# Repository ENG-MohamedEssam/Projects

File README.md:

# Projects
This repository contains most of the projects i made during the last 4 years,
whether those projects were software (AVR32, ARM, Arduino) or Hardware . 

Note that nearly all the files presented whether it was Software or Hardware was created by me.

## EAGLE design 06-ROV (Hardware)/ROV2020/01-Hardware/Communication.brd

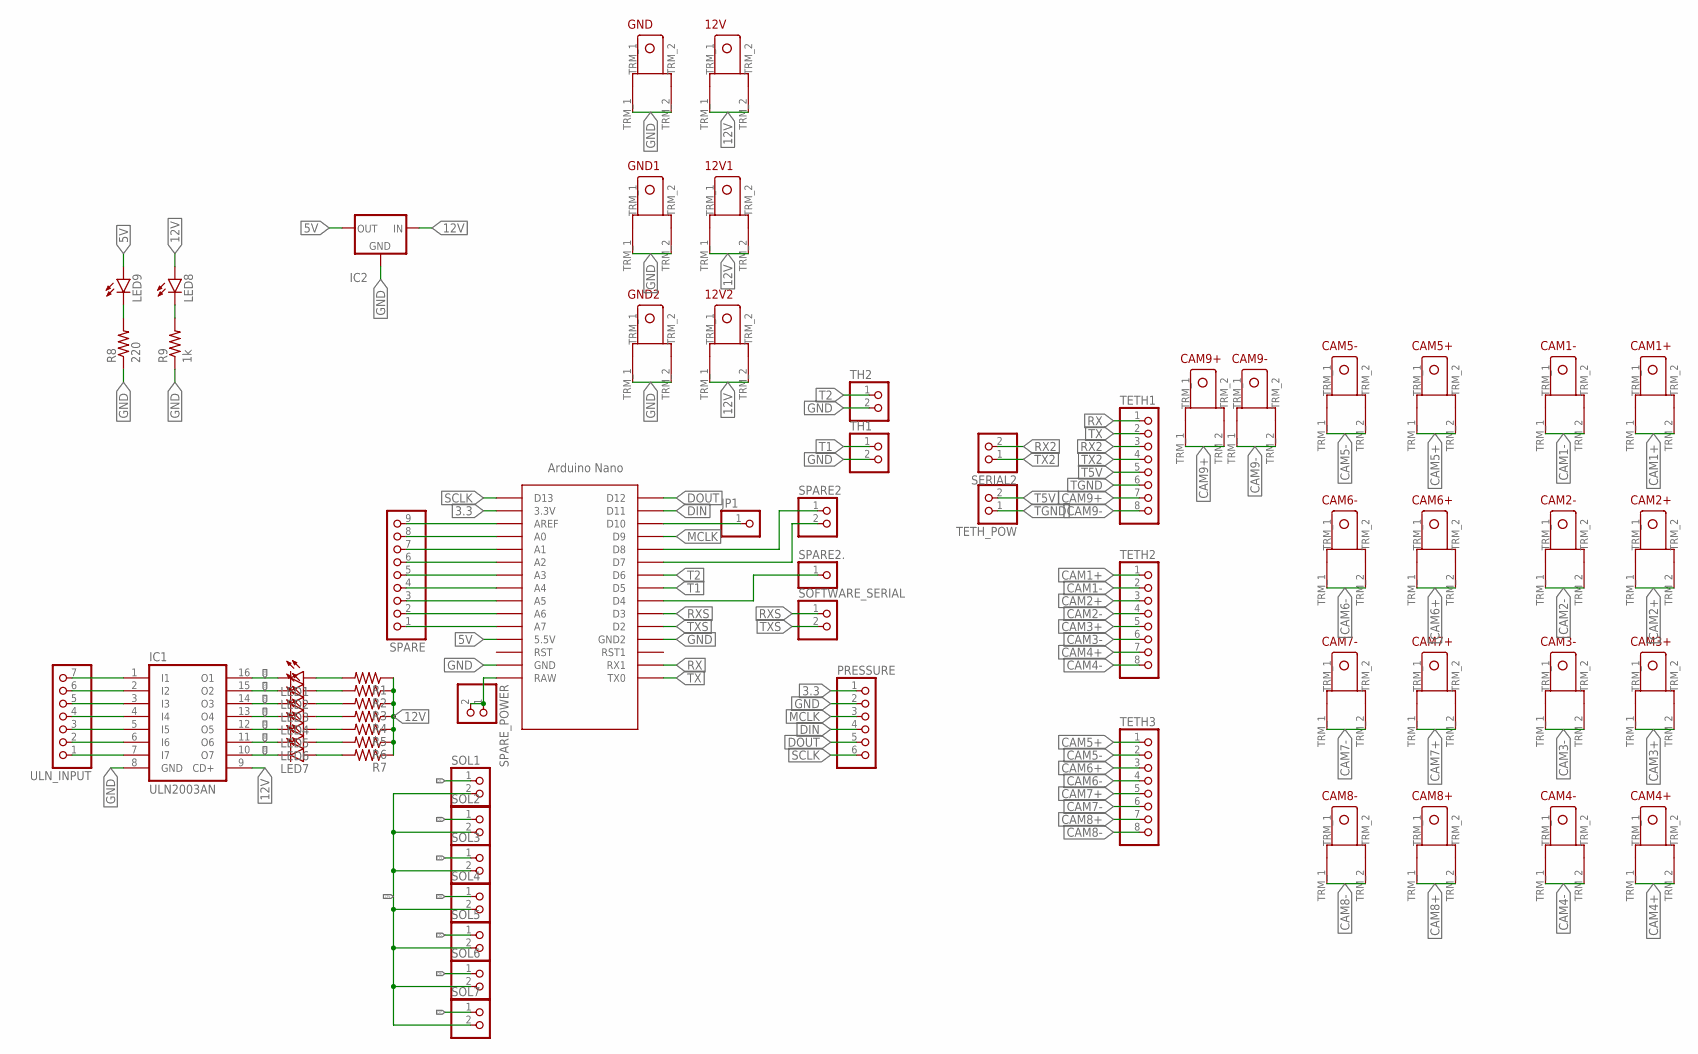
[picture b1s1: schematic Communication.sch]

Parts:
12V, 12V1, 12V2: TERMINAL_EDITED
CAM1+, CAM1-, CAM2+, CAM2-, CAM3+, CAM3-, CAM4+, CAM4-, CAM5+, CAM5-, CAM6+, CAM6-, CAM7+, CAM7-, CAM8+, CAM8-, CAM9+, CAM9-: TERMINAL_EDITED
GND, GND1, GND2: TERMINAL_EDITED
IC1: ULN2003AN; DIL16
IC2: 78XX-METAL; TO3-79
JP1: PINHD-1X1; 1X01
LED1, LED2, LED3, LED4, LED5, LED6, LED7, LED8, LED9: LED5MM
PRESSURE: PINHD-6_DATA; 1X06_DATA
R1, R2, R3, R4, R5, R6, R7: R-US_0204/7; 0204/7
R8: 220; 0204/7
R9: 1k; 0204/7
SERIAL2: PINHD-2_DATA; 1X02_DATA
SOFTWARE_SERIAL: PINHD-2_DATA; 1X02_DATA
SOL1, SOL2, SOL3, SOL4, SOL5, SOL6, SOL7: PINHD-2_DATA; 1X02_DATA
SPARE: PINHD-1X9; 1X09
SPARE2: PINHD-2_DATA; 1X02_DATA
SPARE2.: PINHD-1X1; 1X01
SPARE_POWER: PINHD-2_DATA; 1X02_DATA
TETH1, TETH2, TETH3: PINHD-8_DATA; 1X08_DATA
TETH_POW: PINHD-2_DATA; 1X02_DATA
TH1, TH2: PINHD-2_DATA; 1X02_DATA
U$1: ARDUINO_NANO; NANO
ULN_INPUT: PINHD-1X7; 1X07

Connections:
3.3: PRESSURE.1, U$1.3.3V
5V: IC2.1 (OUT), LED9.A, U$1.5V (5.5V)
12V: 12V.TRM_1, 12V.TRM_2, 12V1.TRM_1, 12V1.TRM_2, 12V2.TRM_1, 12V2.TRM_2, IC1.9 (CD+), IC2.3 (IN), LED8.A, R1.1, R2.1, R3.1, R4.1, R5.1, R6.1, R7.1, SOL1.2, SOL2.2, SOL3.2, SOL4.2, SOL5.2, SOL6.2, SOL7.2
CAM1+: CAM1+.TRM_1, CAM1+.TRM_2, TETH2.1
CAM1-: CAM1-.TRM_1, CAM1-.TRM_2, TETH2.2
CAM2+: CAM2+.TRM_1, CAM2+.TRM_2, TETH2.3
CAM2-: CAM2-.TRM_1, CAM2-.TRM_2, TETH2.4
CAM3+: CAM3+.TRM_1, CAM3+.TRM_2, TETH2.5
CAM3-: CAM3-.TRM_1, CAM3-.TRM_2, TETH2.6
CAM4+: CAM4+.TRM_1, CAM4+.TRM_2, TETH2.7
CAM4-: CAM4-.TRM_1, CAM4-.TRM_2, TETH2.8
CAM5+: CAM5+.TRM_1, CAM5+.TRM_2, TETH3.1
CAM5-: CAM5-.TRM_1, CAM5-.TRM_2, TETH3.2
CAM6+: CAM6+.TRM_1, CAM6+.TRM_2, TETH3.3
CAM6-: CAM6-.TRM_1, CAM6-.TRM_2, TETH3.4
CAM7+: CAM7+.TRM_1, CAM7+.TRM_2, TETH3.5
CAM7-: CAM7-.TRM_1, CAM7-.TRM_2, TETH3.6
CAM8+: CAM8+.TRM_1, CAM8+.TRM_2, TETH3.7
CAM8-: CAM8-.TRM_1, CAM8-.TRM_2, TETH3.8
CAM9+: CAM9+.TRM_1, CAM9+.TRM_2, TETH1.7
CAM9-: CAM9-.TRM_1, CAM9-.TRM_2, TETH1.8
DIN: PRESSURE.4, U$1.D11
DOUT: PRESSURE.5, U$1.D12
GND: GND.TRM_1, GND.TRM_2, GND1.TRM_1, GND1.TRM_2, GND2.TRM_1, GND2.TRM_2, IC1.8 (GND), IC2.2 (GND), PRESSURE.2, R8.1, R9.1, TH1.2, TH2.2, U$1.GND, U$1.GND1 (GND2)
MCLK: PRESSURE.3, U$1.D9
unnamed: SPARE_POWER.1, SPARE_POWER.2, U$1.RAW
unnamed: SPARE.9, U$1.AREF
unnamed: SPARE.8, U$1.A0
unnamed: SPARE.7, U$1.A1
unnamed: SPARE.6, U$1.A2
unnamed: SPARE.5, U$1.A3
unnamed: LED9.K (C), R8.2
unnamed: IC1.7 (I7), ULN_INPUT.1
unnamed: IC1.6 (I6), ULN_INPUT.2
unnamed: IC1.5 (I5), ULN_INPUT.3
unnamed: SPARE.4, U$1.A4
unnamed: SPARE.3, U$1.A5
unnamed: SPARE.2, U$1.A6
unnamed: SPARE.1, U$1.A7
unnamed: IC1.4 (I4), ULN_INPUT.4
unnamed: IC1.3 (I3), ULN_INPUT.5
unnamed: IC1.2 (I2), ULN_INPUT.6
unnamed: IC1.1 (I1), ULN_INPUT.7
unnamed: SPARE2.1, U$1.D8
unnamed: LED1.A, R1.2
unnamed: LED2.A, R2.2
unnamed: JP1.1, U$1.D10
unnamed: LED8.K (C), R9.2
unnamed: LED3.A, R3.2
unnamed: LED4.A, R4.2
unnamed: SPARE2.2, U$1.D7
unnamed: SPARE2..1, U$1.D4
unnamed: LED5.A, R5.2
unnamed: LED6.A, R6.2
unnamed: LED7.A, R7.2
O1: IC1.16 (O1), LED1.K (C), SOL1.1
O2: IC1.15 (O2), LED2.K (C), SOL2.1
O3: IC1.14 (O3), LED3.K (C), SOL3.1
O4: IC1.13 (O4), LED4.K (C), SOL4.1
O5: IC1.12 (O5), LED5.K (C), SOL5.1
O6: IC1.11 (O6), LED6.K (C), SOL6.1
O7: IC1.10 (O7), LED7.K (C), SOL7.1
RX: TETH1.1, U$1.RX1
RX2: SERIAL2.2, TETH1.3
RXS: SOFTWARE_SERIAL.1, U$1.D3
SCLK: PRESSURE.6, U$1.D13
T1: TH1.1, U$1.D5
T2: TH2.1, U$1.D6
T5V: TETH1.5, TETH_POW.2
TGND: TETH1.6, TETH_POW.1
TX: TETH1.2, U$1.TX0
TX2: SERIAL2.1, TETH1.4
TXS: SOFTWARE_SERIAL.2, U$1.D2

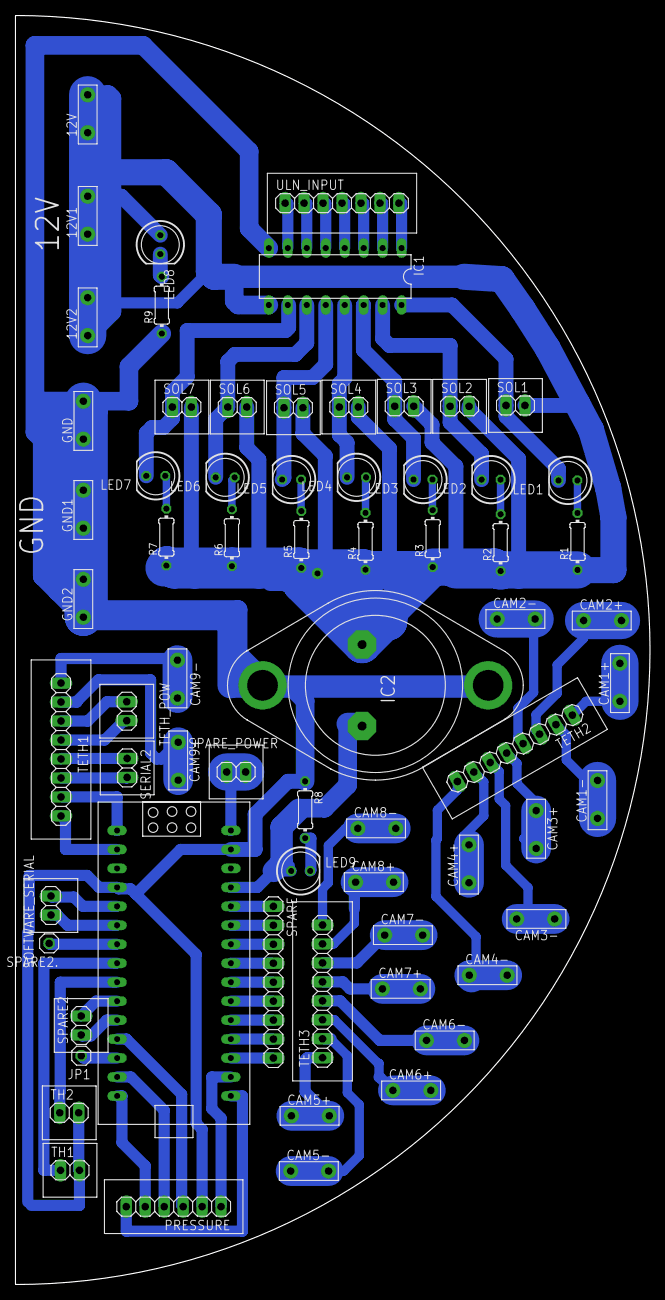
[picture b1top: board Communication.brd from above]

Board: 2 copper layers, 85.0 x 170.0 mm, 67 parts (0 on the bottom side), 73 nets.

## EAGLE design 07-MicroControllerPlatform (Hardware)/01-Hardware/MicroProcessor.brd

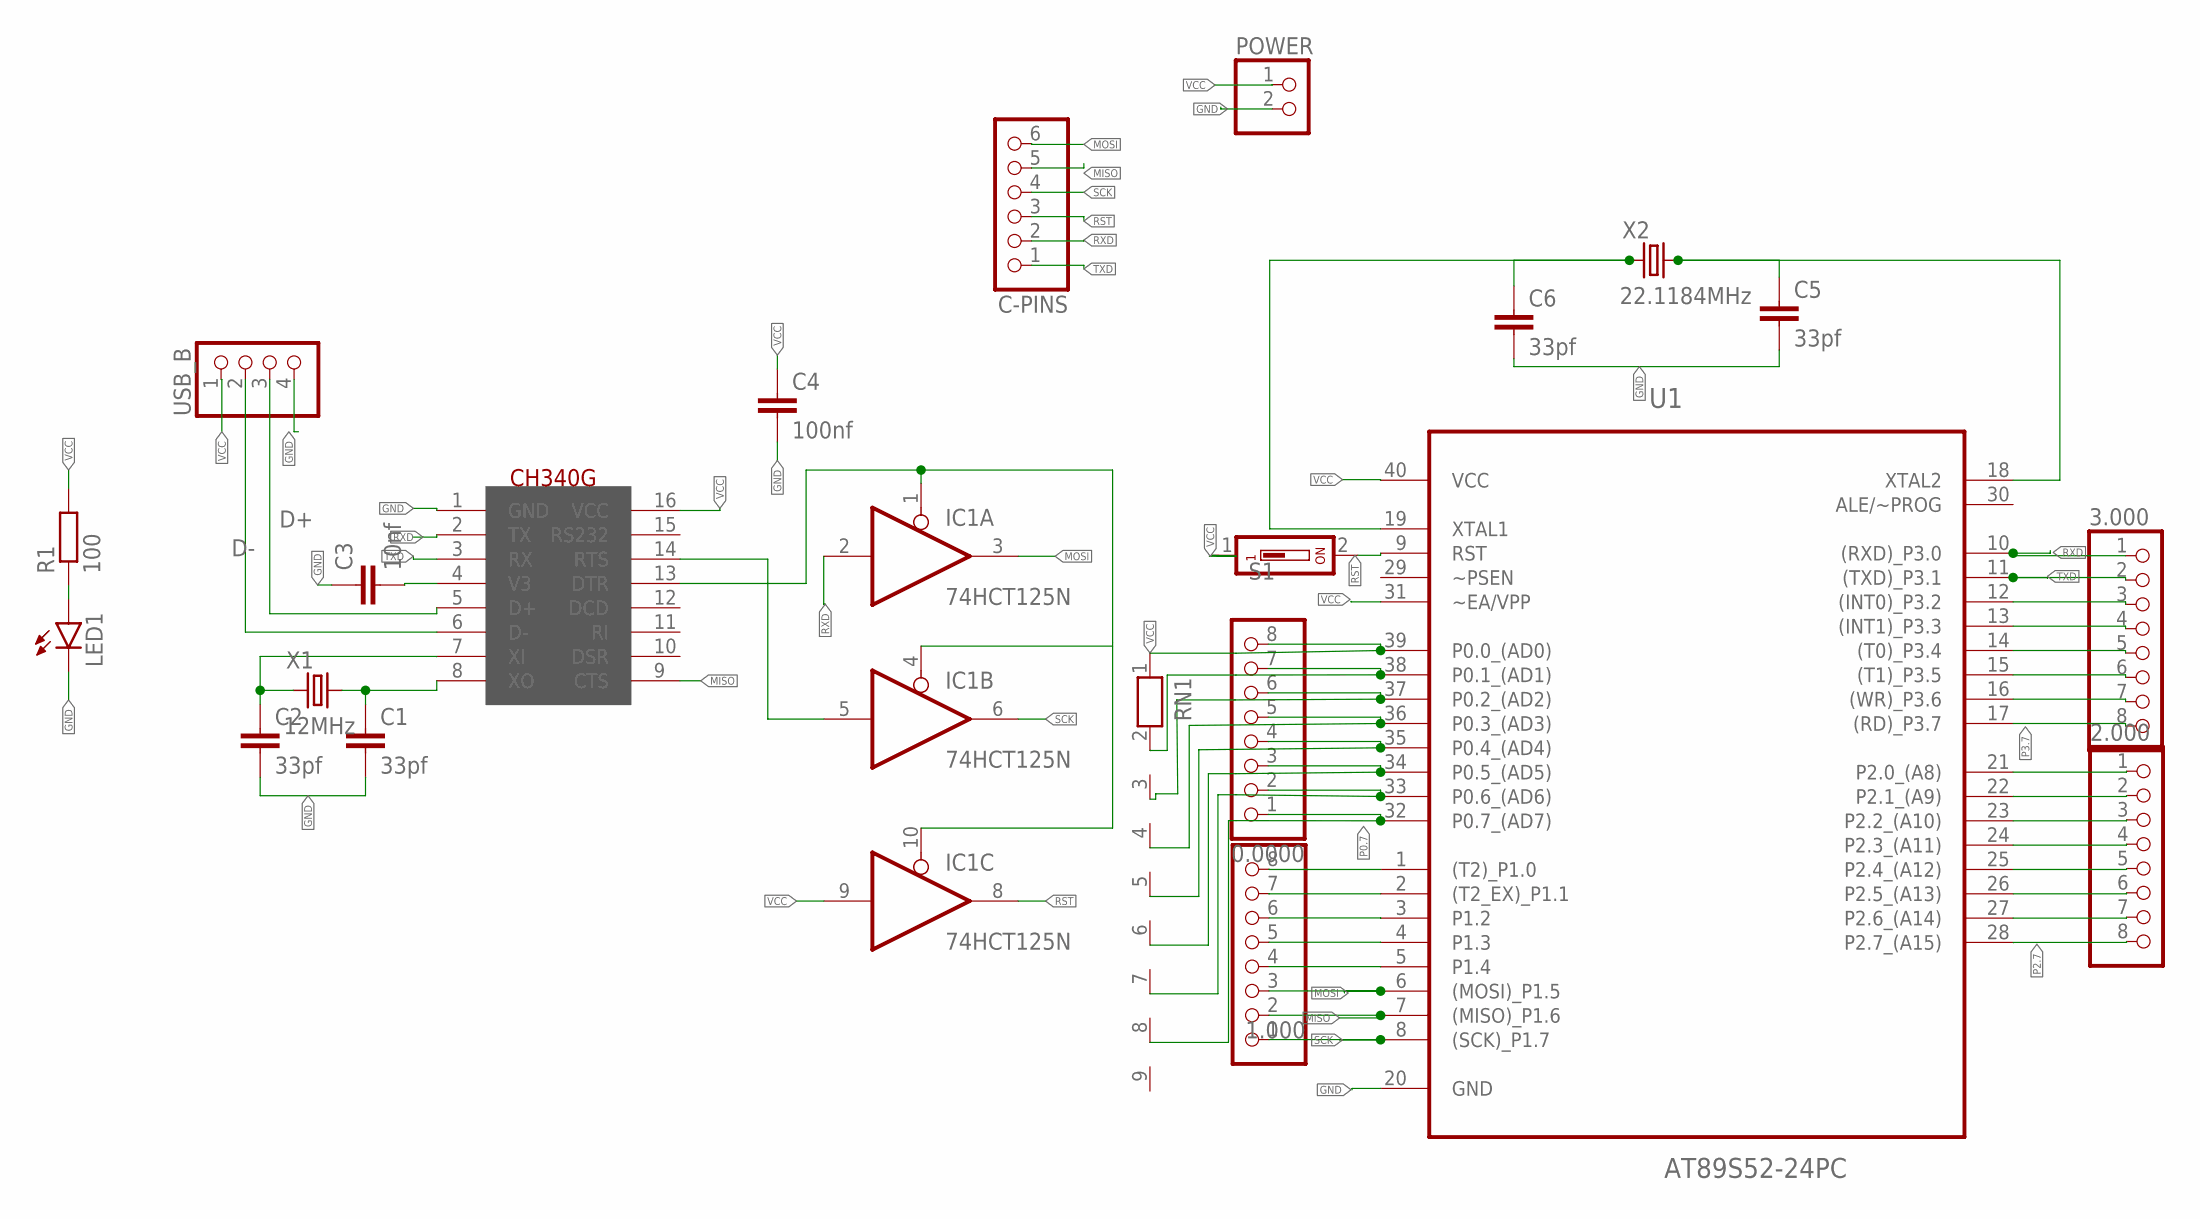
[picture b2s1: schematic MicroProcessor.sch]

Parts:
0.0000, 1.000, 2.000, 3.000: PINHD-1X8; 1X08
C1, C2, C5, C6: 33pf; C025-025X050
C3: 10nf; C025-025X050
C4: 100nf; C025-025X050
C-PINS: PINHD-1X6; 1X06
IC1: 74HCT125N; DIL14
LED1: LED5MM
POWER: PINHD-1X2; 1X02
R1: 100; 0204/7
RN1: RN08; RN-9
S1: SD4-01
U1: AT89S52-24PC; DIP254P1524X482-40
U$1: CH340G; SOIC16
USB_B: PINHD-1X4; 1X04
X1: 12MHz; XTAL_HC49
X2: 22.1184MHz; XTAL_HC49

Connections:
D+: U$1.5 (D+), USB_B.3
D-: U$1.6 (D-), USB_B.2
GND: C1.2, C2.2, C3.1, C4.2, C5.2, C6.2, IC1.7 (GND), LED1.K (C), POWER.2, U1.20 (GND), U$1.1 (GND), USB_B.4
MISO: 1.000.2, C-PINS.5, U1.7 ((MISO)_P1.6), U$1.9 (CTS)
MOSI: 1.000.3, C-PINS.6, IC1.3 (O), U1.6 ((MOSI)_P1.5)
unnamed: LED1.A, R1.1
unnamed: C2.1, U$1.7 (XI), X1.1
unnamed: C1.1, U$1.8 (XO), X1.2
unnamed: C3.2, U$1.4 (V3)
unnamed: IC1.1 (OE), IC1.4 (OE), IC1.10 (OE), U$1.13 (DTR)
unnamed: IC1.5 (I), U$1.14 (RTS)
unnamed: C6.1, U1.19 (XTAL1), X2.1
unnamed: 0.0000.7, RN1.2, U1.38 (P0.1_(AD1))
unnamed: 0.0000.6, RN1.3, U1.37 (P0.2_(AD2))
unnamed: 0.0000.5, RN1.4, U1.36 (P0.3_(AD3))
unnamed: 0.0000.4, RN1.5, U1.35 (P0.4_(AD4))
unnamed: 0.0000.3, RN1.6, U1.34 (P0.5_(AD5))
unnamed: 0.0000.2, RN1.7, U1.33 (P0.6_(AD6))
unnamed: 1.000.8, U1.1 ((T2)_P1.0)
unnamed: C5.1, U1.18 (XTAL2), X2.2
unnamed: 2.000.1, U1.21 (P2.0_(A8))
unnamed: 2.000.2, U1.22 (P2.1_(A9))
unnamed: 2.000.3, U1.23 (P2.2_(A10))
unnamed: 2.000.4, U1.24 (P2.3_(A11))
unnamed: 2.000.5, U1.25 (P2.4_(A12))
unnamed: 2.000.6, U1.26 (P2.5_(A13))
unnamed: 2.000.7, U1.27 (P2.6_(A14))
unnamed: 1.000.7, U1.2 ((T2_EX)_P1.1)
unnamed: 3.000.3, U1.12 ((INT0)_P3.2)
unnamed: 3.000.4, U1.13 ((INT1)_P3.3)
unnamed: 3.000.5, U1.14 ((T0)_P3.4)
unnamed: 3.000.6, U1.15 ((T1)_P3.5)
unnamed: 3.000.7, U1.16 ((WR)_P3.6)
unnamed: 1.000.6, U1.3 (P1.2)
unnamed: 1.000.5, U1.4 (P1.3)
unnamed: 1.000.4, U1.5 (P1.4)
P0.7: 0.0000.1, RN1.8, U1.32 (P0.7_(AD7))
P2.7: 2.000.8, U1.28 (P2.7_(A15))
P3.7: 3.000.8, U1.17 ((RD)_P3.7)
RST: C-PINS.3, IC1.8 (O), S1.2, U1.9 (RST)
RXD: 3.000.1, C-PINS.2, IC1.2 (I), U1.10 ((RXD)_P3.0), U$1.2 (TX)
SCK: 1.000.1, C-PINS.4, IC1.6 (O), U1.8 ((SCK)_P1.7)
TXD: 3.000.2, C-PINS.1, U1.11 ((TXD)_P3.1), U$1.3 (RX)
VCC: 0.0000.8, C4.1, IC1.9 (I), IC1.14 (VCC), POWER.1, R1.2, RN1.1, S1.1, U1.31 (~EA/VPP), U1.39 (P0.0_(AD0)), U1.40 (VCC), U$1.16 (VCC), USB_B.1

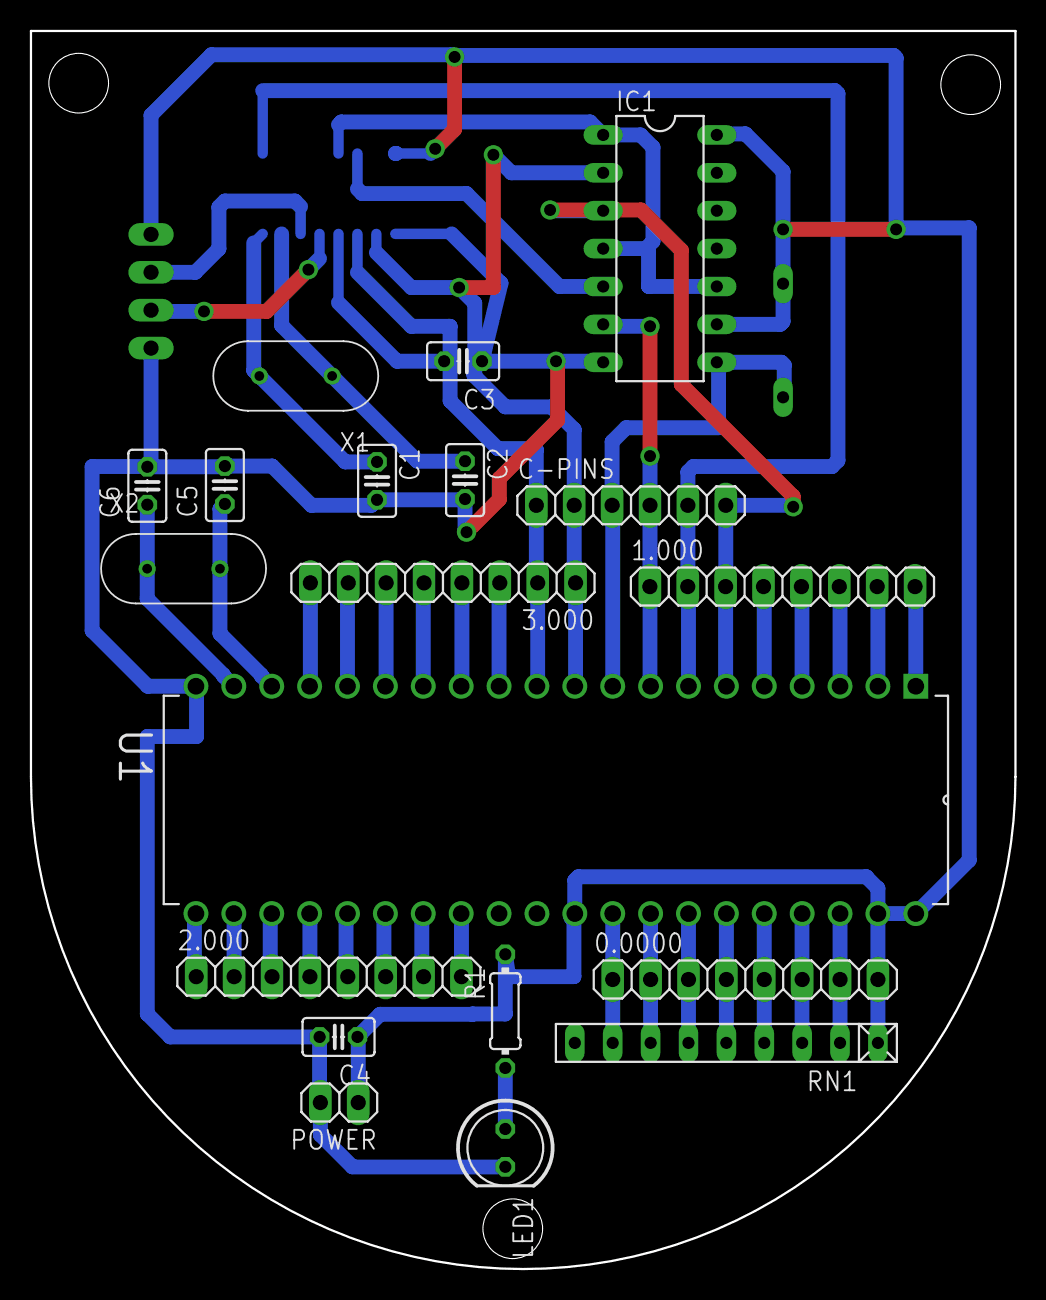
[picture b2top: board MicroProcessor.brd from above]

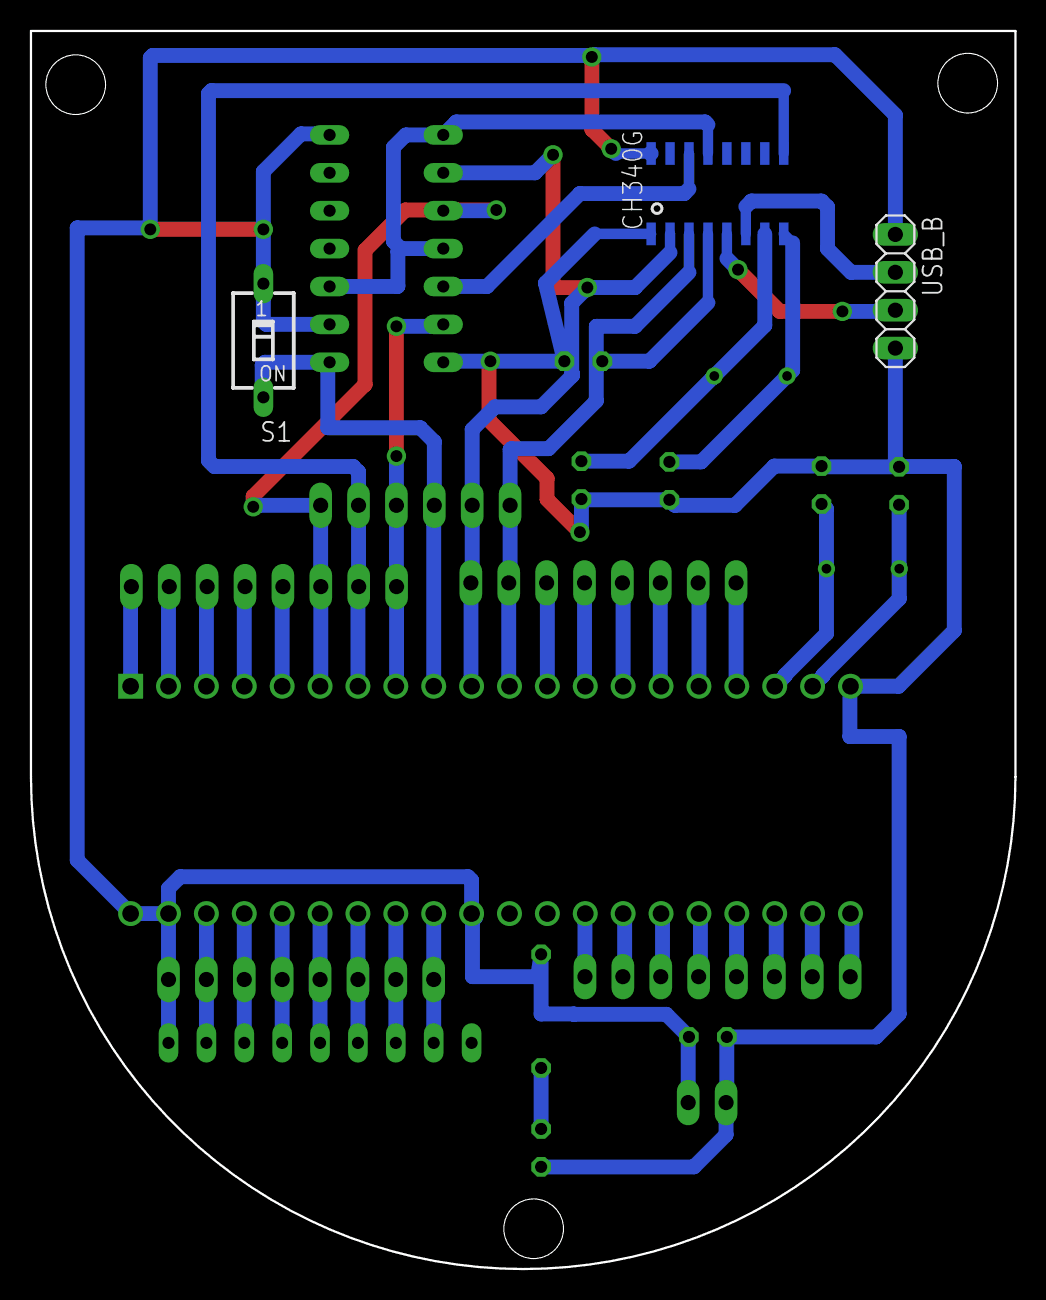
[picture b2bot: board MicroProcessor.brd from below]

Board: 2 copper layers, 66.0 x 83.0 mm, 22 parts (3 on the bottom side), 44 nets.

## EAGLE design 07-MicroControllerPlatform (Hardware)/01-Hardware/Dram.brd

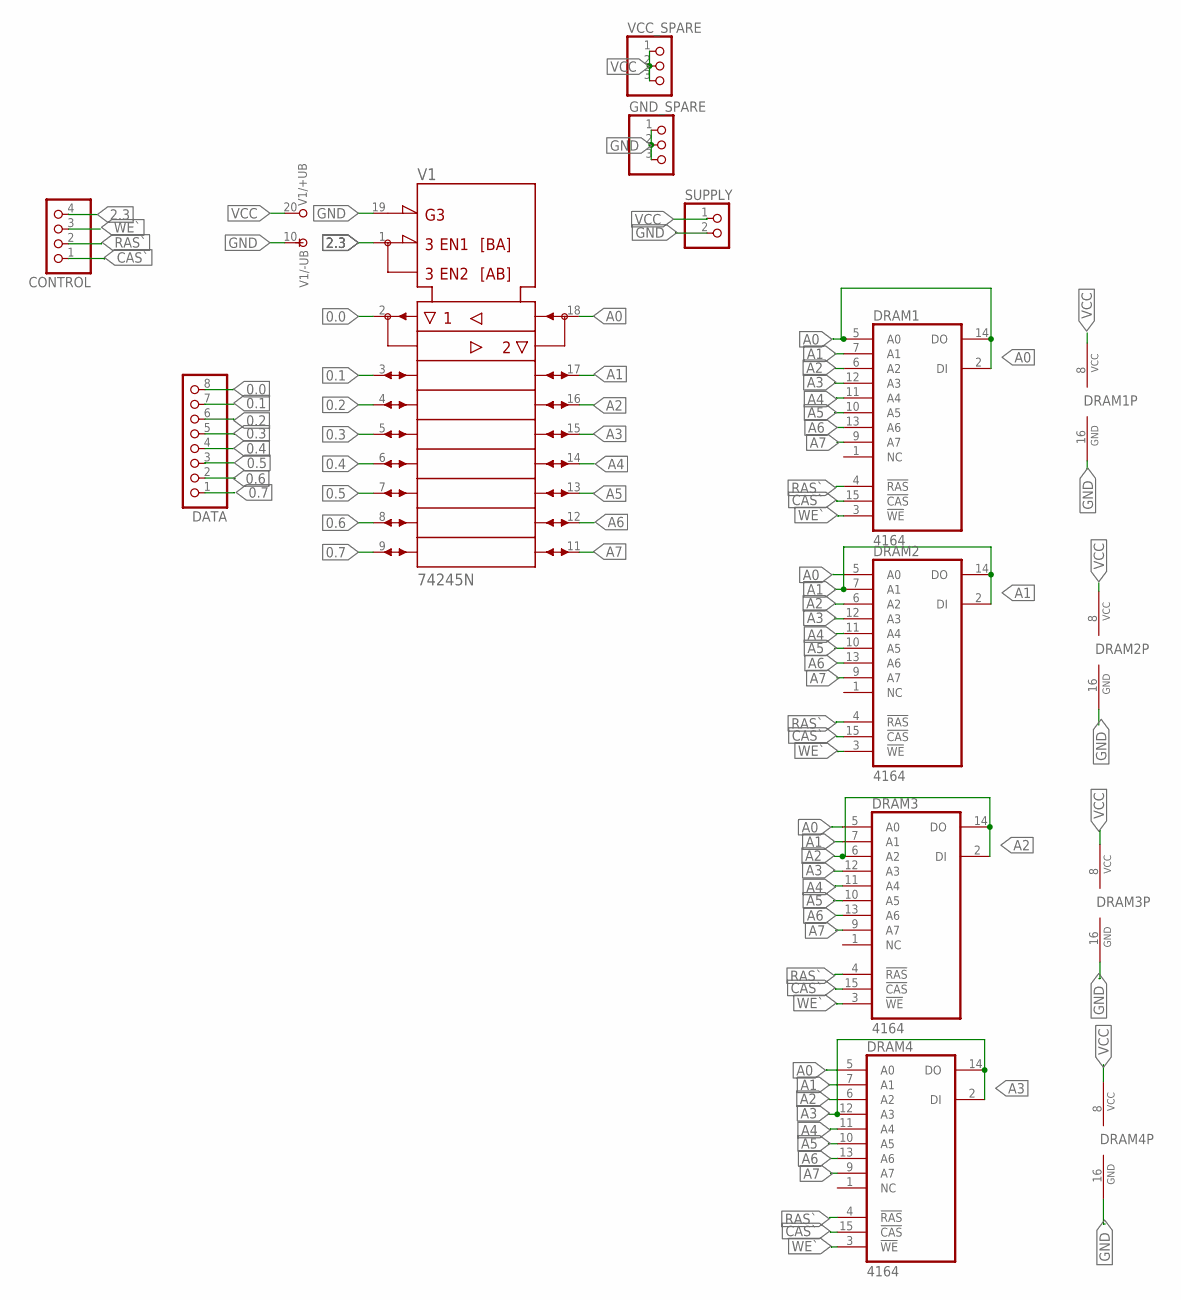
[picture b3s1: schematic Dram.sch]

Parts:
CONTROL: PINHD-1X4; 1X04
DATA: PINHD-1X8; 1X08
DRAM1, DRAM2, DRAM3, DRAM4: 4164; DIP762W53P254L1969H508Q16B
GND_SPARE: PINHD-1X3; 1X03
SUPPLY: PINHD-1X2; 1X02
V1: 74245N; DIL20
VCC_SPARE: PINHD-1X3; 1X03

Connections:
0.0: DATA.8, V1.2 (A1)
0.1: DATA.7, V1.3 (A2)
0.2: DATA.6, V1.4 (A3)
0.3: DATA.5, V1.5 (A4)
0.4: DATA.4, V1.6 (A5)
0.5: DATA.3, V1.7 (A6)
0.6: DATA.2, V1.8 (A7)
0.7: DATA.1, V1.9 (A8)
2.3: CONTROL.4, V1.1 (DIR)
A0: DRAM1.2 (DI), DRAM1.5 (A0), DRAM1.14 (DO), DRAM2.5 (A0), DRAM3.5 (A0), DRAM4.5 (A0), V1.18 (B1)
A1: DRAM1.7 (A1), DRAM2.2 (DI), DRAM2.7 (A1), DRAM2.14 (DO), DRAM3.7 (A1), DRAM4.7 (A1), V1.17 (B2)
A2: DRAM1.6 (A2), DRAM2.6 (A2), DRAM3.2 (DI), DRAM3.6 (A2), DRAM3.14 (DO), DRAM4.6 (A2), V1.16 (B3)
A3: DRAM1.12 (A3), DRAM2.12 (A3), DRAM3.12 (A3), DRAM4.2 (DI), DRAM4.12 (A3), DRAM4.14 (DO), V1.15 (B4)
A4: DRAM1.11 (A4), DRAM2.11 (A4), DRAM3.11 (A4), DRAM4.11 (A4), V1.14 (B5)
A5: DRAM1.10 (A5), DRAM2.10 (A5), DRAM3.10 (A5), DRAM4.10 (A5), V1.13 (B6)
A6: DRAM1.13 (A6), DRAM2.13 (A6), DRAM3.13 (A6), DRAM4.13 (A6), V1.12 (B7)
A7: DRAM1.9 (A7), DRAM2.9 (A7), DRAM3.9 (A7), DRAM4.9 (A7), V1.11 (B8)
CAS`: CONTROL.1, DRAM1.15 (!CAS), DRAM2.15 (!CAS), DRAM3.15 (!CAS), DRAM4.15 (!CAS)
GND: DRAM1.16 (GND), DRAM2.16 (GND), DRAM3.16 (GND), DRAM4.16 (GND), GND_SPARE.1, GND_SPARE.2, GND_SPARE.3, SUPPLY.2, V1.10 (-UB), V1.19 (!G)
RAS`: CONTROL.2, DRAM1.4 (!RAS), DRAM2.4 (!RAS), DRAM3.4 (!RAS), DRAM4.4 (!RAS)
VCC: DRAM1.8 (VCC), DRAM2.8 (VCC), DRAM3.8 (VCC), DRAM4.8 (VCC), SUPPLY.1, V1.20 (+UB), VCC_SPARE.1, VCC_SPARE.2, VCC_SPARE.3
WE`: CONTROL.3, DRAM1.3 (!WE), DRAM2.3 (!WE), DRAM3.3 (!WE), DRAM4.3 (!WE)

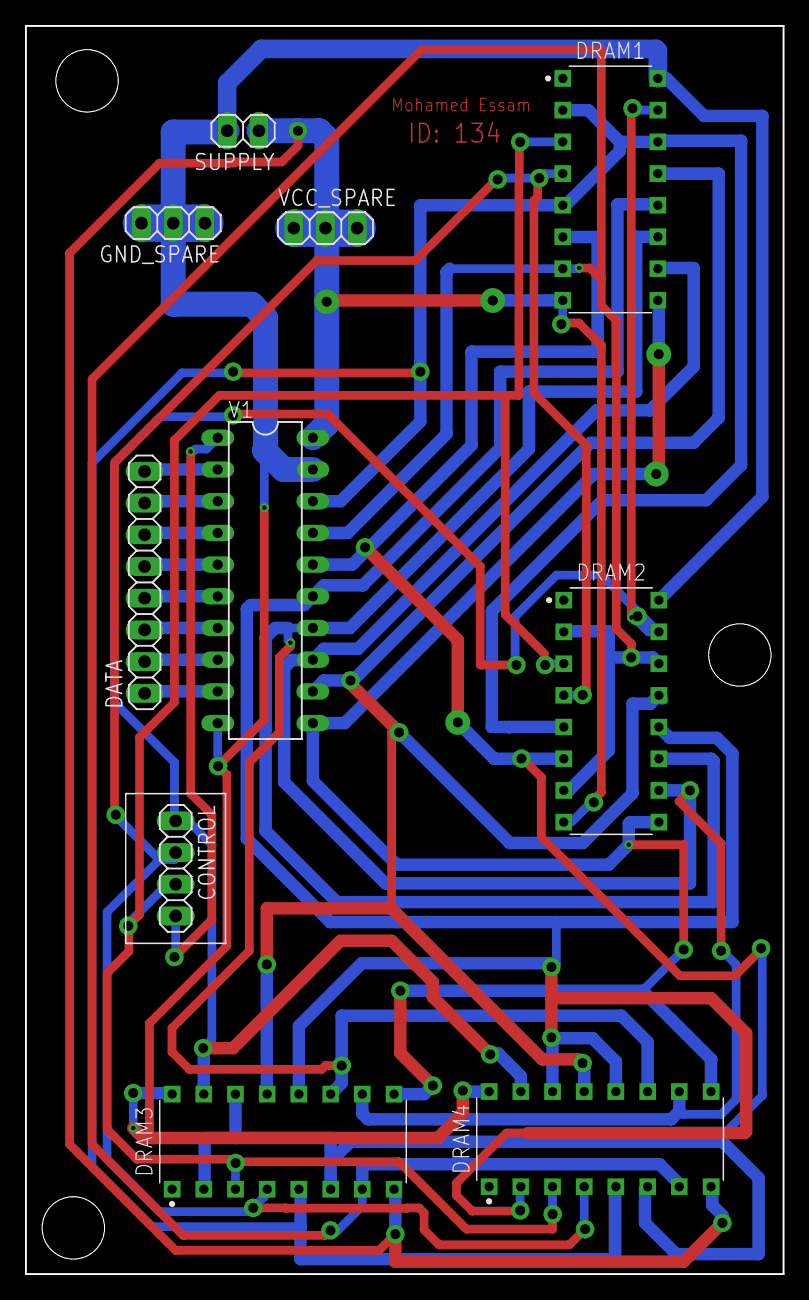
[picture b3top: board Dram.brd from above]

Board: 2 copper layers, 60.7 x 100.0 mm, 10 parts (0 on the bottom side), 22 nets.

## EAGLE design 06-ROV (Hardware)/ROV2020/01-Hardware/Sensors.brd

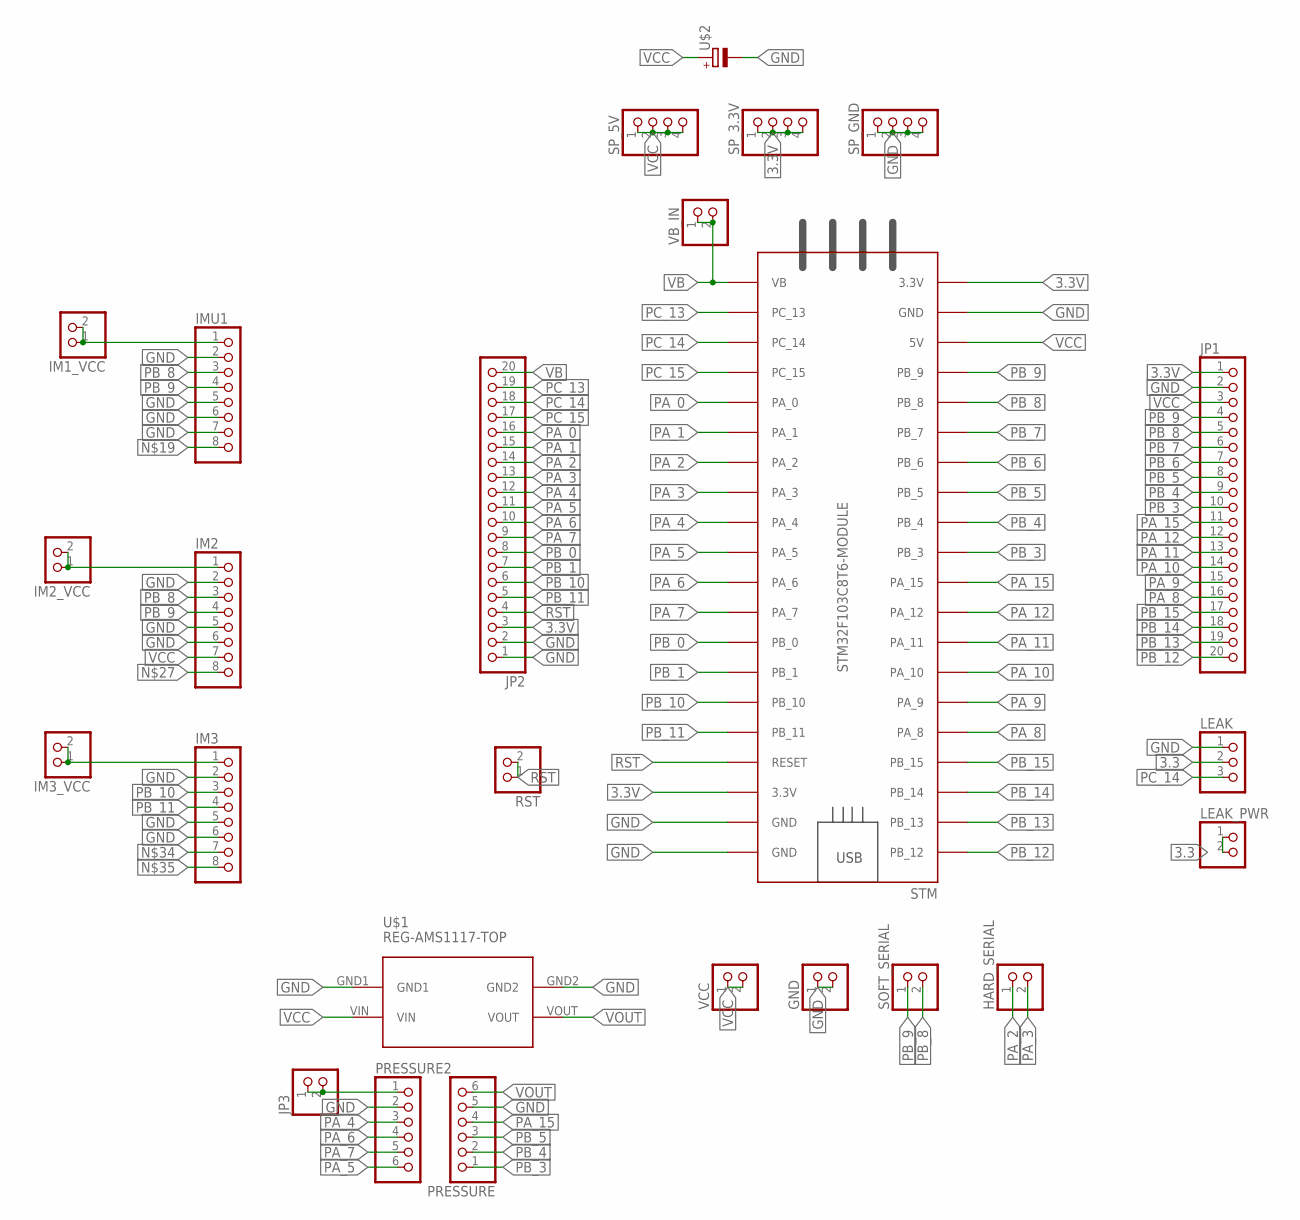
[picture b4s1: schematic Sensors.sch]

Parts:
GND: PINHD-2_DATA; 1X02_DATA
HARD_SERIAL: PINHD-2_DATA; 1X02_DATA
IM1_VCC, IM2_VCC, IM3_VCC: PINHD-2_DATA; 1X02_DATA
IM2, IM3: PINHD-8_DATA; 1X08_DATA
IMU1: PINHD-8_DATA; 1X08_DATA
JP1, JP2: PINHD-1X20; 1X20
JP3: PINHD-2_DATA; 1X02_DATA
LEAK: PINHD-3_DATA; 1X03_DATA
LEAK_PWR: PINHD-2_DATA; 1X02_DATA
PRESSURE, PRESSURE2: PINHD-6_DATA; 1X06_DATA
RST: PINHD-2_DATA; 1X02_DATA
SOFT_SERIAL: PINHD-2_DATA; 1X02_DATA
SP_3.3V, SP_5V: PINHD-1X4; 1X04
SP_GND: PINHD-1X4; 1X04
STM: STM32F103C8T6-MODULE
U$1: REG-AMS1117-TOP; REG-AMS1117_TOP
U$2: CAP_POL; E3,5-8
VB_IN: PINHD-2_DATA; 1X02_DATA
VCC: PINHD-2_DATA; 1X02_DATA

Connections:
3.3: LEAK.2, LEAK_PWR.1, LEAK_PWR.2
3.3V: JP1.1, JP2.3, SP_3.3V.1, SP_3.3V.2, SP_3.3V.3, SP_3.3V.4, STM.3.3V_1 (3.3V), STM.3.3V_2 (3.3V)
GND: GND.1, GND.2, IM2.2, IM2.5, IM2.6, IM3.2, IM3.5, IM3.6, IMU1.2, IMU1.5, IMU1.6, IMU1.7, JP1.2, JP2.1, JP2.2, LEAK.1, PRESSURE.5, PRESSURE2.2, SP_GND.1, SP_GND.2, SP_GND.3, SP_GND.4, STM.GND_1 (GND), STM.GND_2 (GND), STM.GND_3 (GND), U$1.GND1, U$1.GND2, U$2.-
unnamed: IM2.1, IM2_VCC.1, IM2_VCC.2
unnamed: IM1_VCC.1, IM1_VCC.2, IMU1.1
unnamed: IM3.1, IM3_VCC.1, IM3_VCC.2
NS: JP3.1, JP3.2, PRESSURE2.1
PA_0: JP2.16, STM.PA_0
PA_1: JP2.15, STM.PA_1
PA_2: HARD_SERIAL.1, JP2.14, STM.PA_2
PA_3: HARD_SERIAL.2, JP2.13, STM.PA_3
PA_4: JP2.12, PRESSURE2.3, STM.PA_4
PA_5: JP2.11, PRESSURE2.6, STM.PA_5
PA_6: JP2.10, PRESSURE2.4, STM.PA_6
PA_7: JP2.9, PRESSURE2.5, STM.PA_7
PA_8: JP1.16, STM.PA_8
PA_9: JP1.15, STM.PA_9
PA_10: JP1.14, STM.PA_10
PA_11: JP1.13, STM.PA_11
PA_12: JP1.12, STM.PA_12
PA_15: JP1.11, PRESSURE.4, STM.PA_15
PB_0: JP2.8, STM.PB_0
PB_1: JP2.7, STM.PB_1
PB_3: JP1.10, PRESSURE.1, STM.PB_3
PB_4: JP1.9, PRESSURE.2, STM.PB_4
PB_5: JP1.8, PRESSURE.3, STM.PB_5
PB_6: JP1.7, STM.PB_6
PB_7: JP1.6, STM.PB_7
PB_8: IM2.3, IMU1.3, JP1.5, SOFT_SERIAL.2, STM.PB_8
PB_9: IM2.4, IMU1.4, JP1.4, SOFT_SERIAL.1, STM.PB_9
PB_10: IM3.3, JP2.6, STM.PB_10
PB_11: IM3.4, JP2.5, STM.PB_11
PB_12: JP1.20, STM.PB_12
PB_13: JP1.19, STM.PB_13
PB_14: JP1.18, STM.PB_14
PB_15: JP1.17, STM.PB_15
PC_13: JP2.19, STM.PC_13
PC_14: JP2.18, LEAK.3, STM.PC_14
PC_15: JP2.17, STM.PC_15
RST: JP2.4, RST.1, RST.2, STM.RESET
VB: JP2.20, STM.VB, VB_IN.1, VB_IN.2
VCC: IM2.7, JP1.3, SP_5V.1, SP_5V.2, SP_5V.3, SP_5V.4, STM.5V, U$1.VIN, U$2.+, VCC.1, VCC.2
VOUT: PRESSURE.6, U$1.VOUT

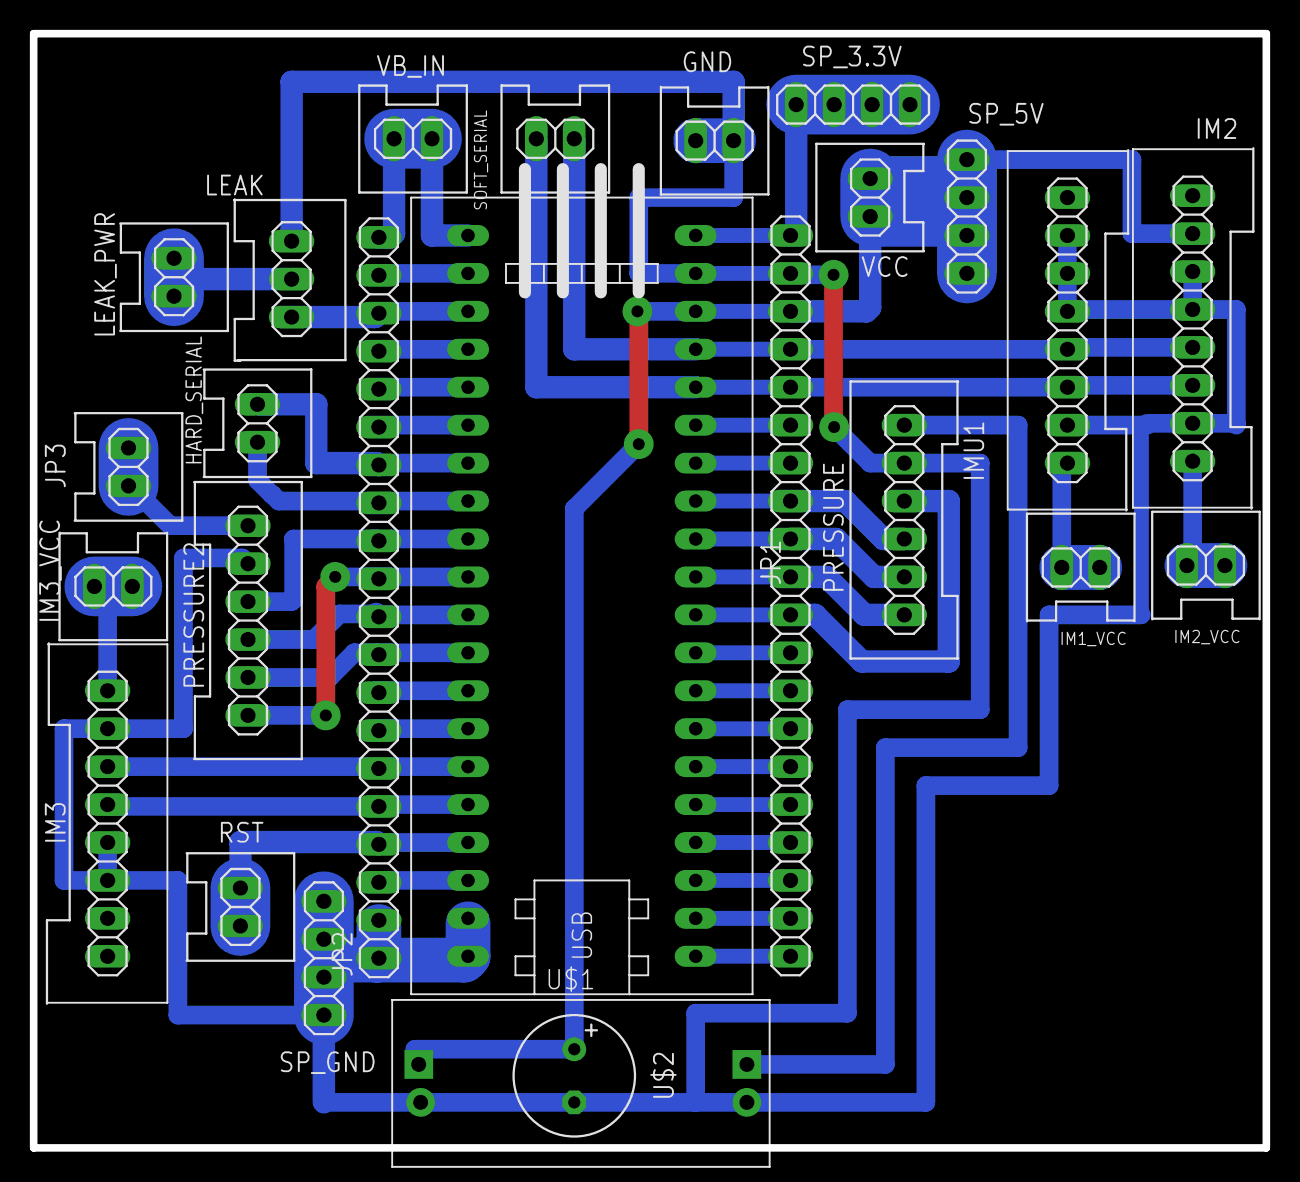
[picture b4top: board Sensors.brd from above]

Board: 2 copper layers, 82.5 x 74.6 mm, 25 parts (0 on the bottom side), 43 nets.

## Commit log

2022-11-29 Just an edit in readme file
2022-12-11 Change in the whole code
